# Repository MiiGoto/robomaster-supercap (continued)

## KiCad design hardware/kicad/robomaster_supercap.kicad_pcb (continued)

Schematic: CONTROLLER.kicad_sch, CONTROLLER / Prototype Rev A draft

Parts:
C40, C41, C42, C43, C46, C48: 100nF / 16V X7R; C_0805_2012Metric; MPN C0805C104K5RACTU
C44: 4.7uF /16V X7R; C_0805_2012Metric; MPN C0805C475K4RACTU
C45, C47: 1uF /16V; C_0805_2012Metric; MPN GRM21BR71H105KA12L
C49: 100nF; C_0805_2012Metric; MPN C0805C104K5RACTU
J6: SWD reference voltage ONLY / do not externally po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; PinHeader_1x06_P2.54mm_Vertical
J7: 3.3V UART / no power pin; PinHeader_1x03_P2.54mm_Vertical
R69: 10R; R_0805_2012Metric; MPN CRCW080510R0FKEA
R70: 0R; R_0805_2012Metric; MPN CRCW08050000Z0EA
R71, R72, R73, R74, R75, R76, R77, R78, R79, R80, R81: 10k; R_0805_2012Metric; MPN CRCW080510K0FKEA
U11: STM32G474RET6; LQFP-64_10x10mm_P0.5mm; MPN STM32G474RET6

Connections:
ARM_PULSE: R77.1 (A), U11.24 (PB0); also elsewhere on the board
BUS_ISO_FB: U11.57 (PB4); also elsewhere on the board
BUS_ISO_REQUEST: U11.38 (PC6); also elsewhere on the board
BUS_I_ADC: U11.18 (PA4); also elsewhere on the board
BUS_RAW_ADC: U11.11 (PC3); also elsewhere on the board
BUS_V_ADC: U11.12 (PA0); also elsewhere on the board
BYP_BUS_FB: U11.59 (PB6); also elsewhere on the board
BYP_BUS_REQUEST: U11.33 (PB11); also elsewhere on the board
BYP_CAP_FB: U11.60 (PB7); also elsewhere on the board
BYP_CAP_REQUEST: U11.41 (PC9); also elsewhere on the board
CAN_RX: R72.1 (A), U11.61 (PB8); also elsewhere on the board
CAN_STANDBY: U11.54 (PC12); also elsewhere on the board
CAN_TX: U11.62 (PB9); also elsewhere on the board
CAP_ISO_FB: U11.58 (PB5); also elsewhere on the board
CAP_ISO_REQUEST: U11.39 (PC7); also elsewhere on the board
CAP_I_ADC: U11.19 (PA5); also elsewhere on the board
CAP_RAW_ADC: U11.22 (PC4); also elsewhere on the board
CAP_V_ADC: U11.13 (PA1); also elsewhere on the board
DUMP_REQUEST: U11.52 (PC10); also elsewhere on the board
GND: C40.2 (B), C41.2 (B), C42.2 (B), C43.2 (B), C44.2 (B), C45.2 (B), C46.2 (B), C47.2 (B), C48.2 (B), C49.2 (B), J6.6, J7.3, R73.2 (B), R74.2 (B), R75.2 (B), R76.2 (B), R77.2 (B), R78.2 (B), R79.2 (B), R80.2 (B), U11.15 (VSS), U11.27 (VSSA), U11.31 (VSS), U11.47 (VSS), U11.63 (VSS); also elsewhere on the board
HW_FAULT_N: U11.46 (PA12); also elsewhere on the board
IL_I_ADC: U11.20 (PA6); also elsewhere on the board
MCU_GATE_REQUEST: R78.1 (A), U11.26 (PB2); also elsewhere on the board
MON_ALERT_HOST: U11.53 (PC11); also elsewhere on the board
MON_CONFIG_VALID: R80.1 (A), U11.55 (PD2); also elsewhere on the board
MON_CS_HOST: R81.1 (A), U11.34 (PB12); also elsewhere on the board
MON_MISO_HOST: U11.36 (PB14); also elsewhere on the board
MON_MOSI_HOST: U11.37 (PB15); also elsewhere on the board
MON_SCLK_HOST: U11.35 (PB13); also elsewhere on the board
NRST: C49.1 (A), J6.5, R71.1 (A), U11.7 (PG10); also elsewhere on the board
PRE_BUS_FB: U11.51 (PA15); also elsewhere on the board
PRE_BUS_REQUEST: U11.30 (PB10); also elsewhere on the board
PRE_CAP_FB: U11.2 (PC13); also elsewhere on the board
PRE_CAP_REQUEST: U11.40 (PC8); also elsewhere on the board
PWM_AH: R73.1 (A), U11.42 (PA8); also elsewhere on the board
PWM_AL: R74.1 (A), U11.43 (PA9); also elsewhere on the board
PWM_BH: R75.1 (A), U11.44 (PA10); also elsewhere on the board
PWM_BL: R76.1 (A), U11.45 (PA11); also elsewhere on the board
REFEREE_PERMIT: U11.23 (PC5); also elsewhere on the board
SWCLK: J6.3, U11.50 (PA14)
SWDIO: J6.2, U11.49 (PA13)
SWO: J6.4, U11.56 (PB3)
TEMP_BANK_ADC: U11.10 (PC2); also elsewhere on the board
TEMP_FET_ADC: U11.8 (PC0); also elsewhere on the board
TEMP_L_ADC: U11.9 (PC1); also elsewhere on the board
UART_RX: J7.2, U11.17 (PA3)
UART_TX: J7.1, U11.14 (PA2)
V3V3: C40.1 (A), C41.1 (A), C42.1 (A), C43.1 (A), C44.1 (A), J6.1, R69.1 (A), R71.2 (B), R72.2 (B), R81.2 (B), U11.1 (VBAT), U11.16 (VDD), U11.32 (VDD), U11.48 (VDD), U11.64 (VDD); also elsewhere on the board
VDDA: C45.1 (A), C46.1 (A), R69.2 (B), R70.1 (A), U11.29 (VDDA)
VREF_ADC: C47.1 (A), C48.1 (A), R70.2 (B), U11.28 (VREF+)
WD_HEARTBEAT: R79.1 (A), U11.25 (PB1); also elsewhere on the board

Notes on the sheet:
PG10 pin7 configured NRST; PB8 pin61 BOOT0 strap/options: boot configuration must be locked to flash before use.
HSI clock for draft, no external crystal. FDCAN bit timing/HSI accuracy must be checked before robot integration.
ADC HRTIM-synchronized sampling; internal comparators are secondary diagnostics, not primary OC shutdown.

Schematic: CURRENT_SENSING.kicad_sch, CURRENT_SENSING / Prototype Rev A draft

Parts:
C50, C52, C53, C54, C56, C57, C58, C60, C61: 100nF / 16V X7R; C_0805_2012Metric; MPN C0805C104K5RACTU
C51, C55, C59: 1nF C0G; C_0805_2012Metric; MPN C0805C102J1GACTU
J8: OC diagnostic outputs / do not load; PinHeader_1x05_P2.54mm_Vertical
R82, R83, R84: 100R; R_0805_2012Metric; MPN CRCW0805100RFKEA
U12: INA240A2D; SOIC-8_3.9x4.9mm_P1.27mm; MPN INA240A2D
U13, U14, U16, U17, U19, U20: INA293A1DBVR; SOT-23-5; MPN INA293A1DBVR
U15, U18: INA240A1D; SOIC-8_3.9x4.9mm_P1.27mm; MPN INA240A1D

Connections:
BUS_FAST_NEG: J8.2, U14.1 (OUT); also elsewhere on the board
BUS_FAST_POS: J8.1, U13.1 (OUT); also elsewhere on the board
BUS_I_FILTER: C51.1 (A), R82.2 (B); also elsewhere on the board
BUS_I_RAW: R82.1 (A), U12.5 (OUT)
BUS_KELVIN_M: U12.1 (INM), U13.4 (INM), U14.3 (INP); also elsewhere on the board
BUS_KELVIN_P: U12.8 (INP), U13.3 (INP), U14.4 (INM); also elsewhere on the board
CAP_FAST_NEG: J8.4, U17.1 (OUT); also elsewhere on the board
CAP_FAST_POS: J8.3, U16.1 (OUT); also elsewhere on the board
CAP_I_FILTER: C55.1 (A), R83.2 (B); also elsewhere on the board
CAP_I_RAW: R83.1 (A), U15.5 (OUT)
CAP_KELVIN_M: U15.1 (INM), U16.4 (INM), U17.3 (INP); also elsewhere on the board
CAP_KELVIN_P: U15.8 (INP), U16.3 (INP), U17.4 (INM); also elsewhere on the board
GND: C50.2 (B), C51.2 (B), C52.2 (B), C53.2 (B), C54.2 (B), C55.2 (B), C56.2 (B), C57.2 (B), C58.2 (B), C59.2 (B), C60.2 (B), C61.2 (B), J8.5, U12.2 (GND), U12.3 (REF2), U13.2 (GND), U14.2 (GND), U15.2 (GND), U15.3 (REF2), U16.2 (GND), U17.2 (GND), U18.2 (GND), U18.3 (REF2), U19.2 (GND), U20.2 (GND); also elsewhere on the board
IL_FAST_NEG: U20.1 (OUT); also elsewhere on the board
IL_FAST_POS: U19.1 (OUT); also elsewhere on the board
IL_I_FILTER: C59.1 (A), R84.2 (B); also elsewhere on the board
IL_I_RAW: R84.1 (A), U18.5 (OUT)
IL_KELVIN_M: U18.1 (INM), U19.4 (INM), U20.3 (INP); also elsewhere on the board
IL_KELVIN_P: U18.8 (INP), U19.3 (INP), U20.4 (INM); also elsewhere on the board
V3V3: C50.1 (A), C52.1 (A), C53.1 (A), C54.1 (A), C56.1 (A), C57.1 (A), C58.1 (A), C60.1 (A), C61.1 (A), U12.6 (VS), U12.7 (REF1), U13.5 (VS), U14.5 (VS), U15.6 (VS), U15.7 (REF1), U16.5 (VS), U17.5 (VS), U18.6 (VS), U18.7 (REF1), U19.5 (VS), U20.5 (VS); also elsewhere on the board

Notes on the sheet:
WSK Kelvin pads2/3 route separately to amplifiers; no power current in sense tracks.
INA240 refs REF1=VS, REF2=GND -> midscale1.65V. +-8A bus and +-20A cap/IL nominal ADC windows.
All fast front ends INA293 CM -4..110V; INA301 rejected because40V absmax is below SMBJ28A45.4V rated clamp.
IL dedicated INA293 opposite polarities, CM -4..110V; PWM edge recovery and latency must be measured.

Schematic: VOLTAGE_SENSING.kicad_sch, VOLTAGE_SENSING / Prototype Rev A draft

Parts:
C62, C63, C64, C65: 4.7nF C0G; C_0805_2012Metric; MPN C0805C472J5GACTU
C66, C67, C68: 100nF / 16V X7R; C_0805_2012Metric; MPN C0805C104K5RACTU
D13, D15, D17, D19: BAT54H signal clamp; D_SOD-123F; MPN BAT54H
D14, D16, D18, D20: BAT54H negative clamp; D_SOD-123F; MPN BAT54H
D21, D22: 1N4148W /100V; D_SOD-123; MPN 1N4148W
R85, R86, R88, R89, R91, R92, R94, R95: 33k /1%; R_0805_2012Metric; MPN CRCW080533K0FKEA
R87, R93: 5.1k /1%; R_0805_2012Metric; MPN CRCW08055K10FKEA
R90, R96: 6.8k /1%; R_0805_2012Metric; MPN CRCW08056K80FKEA
R97: 3.3k /1W; R_2512_6332Metric; MPN CRCW25123K30FKEG
R98: 11.8k /1%; R_0805_2012Metric; MPN CRCW080511K8FKEA
R99: 10k /1%; R_0805_2012Metric; MPN CRCW080510K0FKEA
R100, R101, R102, R103, R104, R105, R106, R107, R108, R109: 100k off leakage drain; R_0805_2012Metric; MPN CRCW0805100KFKEA
U21: TLV431AIDBZR; SOT-23; MPN TLV431AIDBZR
U22, U23, U24: TMUX1511PWR; TSSOP-14_4.4x5mm_P0.65mm; MPN TMUX1511PWR

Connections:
ADC_CLAMP_2V7: D13.1 (K), D15.1 (K), D17.1 (K), D19.1 (K), R97.2 (B), R98.1 (A), U21.2 (K)
BANK_P_RAW: D22.2 (A), R94.1 (A); also elsewhere on the board
BUS_DIV_TOP: R85.2 (B), R86.1 (A)
BUS_FUSED: D21.2 (A), R91.1 (A); also elsewhere on the board
BUS_I_ADC: R104.1 (A), U23.3 (D1); also elsewhere on the board
BUS_I_FILTER: U23.2 (S1); also elsewhere on the board
BUS_LINK: R85.1 (A); also elsewhere on the board
BUS_RAW_ADC: R102.1 (A), U22.8 (D3); also elsewhere on the board
BUS_RAW_DIV_TOP: R91.2 (B), R92.1 (A)
BUS_RAW_V_FILTER: C64.1 (A), D17.2 (A), D18.1 (K), R92.2 (B), R93.1 (A), U22.9 (S3)
BUS_V_ADC: R100.1 (A), U22.3 (D1); also elsewhere on the board
BUS_V_FILTER: C62.1 (A), D13.2 (A), D14.1 (K), R86.2 (B), R87.1 (A), U22.2 (S1)
CAP_DIV_TOP: R88.2 (B), R89.1 (A)
CAP_I_ADC: R105.1 (A), U23.6 (D2); also elsewhere on the board
CAP_I_FILTER: U23.5 (S2); also elsewhere on the board
CAP_LINK: R88.1 (A); also elsewhere on the board
CAP_RAW_ADC: R103.1 (A), U22.11 (D4); also elsewhere on the board
CAP_RAW_DIV_TOP: R94.2 (B), R95.1 (A)
CAP_RAW_V_FILTER: C65.1 (A), D19.2 (A), D20.1 (K), R95.2 (B), R96.1 (A), U22.12 (S4)
CAP_V_ADC: R101.1 (A), U22.6 (D2); also elsewhere on the board
CAP_V_FILTER: C63.1 (A), D15.2 (A), D16.1 (K), R89.2 (B), R90.1 (A), U22.5 (S2)
CLAMP_OR: D21.1 (K), D22.1 (K), R97.1 (A)
CLAMP_REF: R98.2 (B), R99.1 (A), U21.1 (REF)
GND: C62.2 (B), C63.2 (B), C64.2 (B), C65.2 (B), C66.2 (B), C67.2 (B), C68.2 (B), D14.2 (A), D16.2 (A), D18.2 (A), D20.2 (A), R87.2 (B), R90.2 (B), R93.2 (B), R96.2 (B), R99.2 (B), R100.2 (B), R101.2 (B), R102.2 (B), R103.2 (B), R104.2 (B), R105.2 (B), R106.2 (B), R107.2 (B), R108.2 (B), R109.2 (B), U21.3 (A), U22.7 (GND), U23.7 (GND), U24.7 (GND), U24.9 (S3), U24.12 (S4); also elsewhere on the board
IL_I_ADC: R106.1 (A), U23.8 (D3); also elsewhere on the board
IL_I_FILTER: U23.9 (S3); also elsewhere on the board
RAIL_OK: U22.1 (SEL1), U22.4 (SEL2), U22.10 (SEL3), U22.13 (SEL4), U23.1 (SEL1), U23.4 (SEL2), U23.10 (SEL3), U23.13 (SEL4), U24.1 (SEL1), U24.4 (SEL2), U24.10 (SEL3), U24.13 (SEL4); also elsewhere on the board
TEMP_BANK_ADC: R109.1 (A), U24.6 (D2); also elsewhere on the board
TEMP_BANK_FILTER: U24.5 (S2); also elsewhere on the board
TEMP_FET_ADC: R107.1 (A), U23.11 (D4); also elsewhere on the board
TEMP_FET_FILTER: U23.12 (S4); also elsewhere on the board
TEMP_L_ADC: R108.1 (A), U24.3 (D1); also elsewhere on the board
TEMP_L_FILTER: U24.2 (S1); also elsewhere on the board
V3V3: C66.1 (A), C67.1 (A), C68.1 (A), U22.14 (VDD), U23.14 (VDD), U24.14 (VDD); also elsewhere on the board

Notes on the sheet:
TMUX1511 powered-off isolation <=3.6V; independent 2.7V clamp proposal avoids dumping into dead MCU rail.
Divider bus36V ->2.582V; cap24.3V ->2.270V nominal. Clamp forward-V and all partial-power cases MUST VERIFY.
100k ADC-side drain:2uA max powered-off leakage gives0.2V estimate. Include loaded divider/NTC calibration.
Current/NTC outputs are bus-fed; partial-power/backfeed and probe effects remain test gates.

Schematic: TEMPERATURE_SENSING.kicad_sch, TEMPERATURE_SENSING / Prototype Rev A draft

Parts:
C69, C70, C71: 10nF; C_0805_2012Metric; MPN C0805C103J5GACTU
J9: FET NTC probe option; PinHeader_1x02_P2.54mm_Vertical; not fitted
J10: L NTC probe option; PinHeader_1x02_P2.54mm_Vertical; not fitted
J11: BANK NTC probe option; PinHeader_1x02_P2.54mm_Vertical; not fitted
R110, R112, R114: 10k /1%; R_0805_2012Metric; MPN CRCW080510K0FKEA
R111, R113, R115: NTCLE100E3103JB0 /10k NTC B3977; PinHeader_1x02_P2.54mm_Vertical; MPN NTCLE100E3103JB0

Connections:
GND: C69.2 (B), C70.2 (B), C71.2 (B), J9.2, J10.2, J11.2, R111.2 (B), R113.2 (B), R115.2 (B); also elsewhere on the board
TEMP_BANK_FILTER: C71.1 (A), J11.1, R114.2 (B), R115.1 (A); also elsewhere on the board
TEMP_FET_FILTER: C69.1 (A), J9.1, R110.2 (B), R111.1 (A); also elsewhere on the board
TEMP_L_FILTER: C70.1 (A), J10.1, R112.2 (B), R113.1 (A); also elsewhere on the board
V3V3: R110.1 (A), R112.1 (A), R114.1 (A); also elsewhere on the board

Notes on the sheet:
3 representative hotspots; optional connector replaces fitted NTC, not parallel second thermistor.
Open NTC reads high, short reads zero. Firmware faults both extremes; hardware thermal window also in SAFETY.
Trip reference options: bank ~55C, FET/L ~70C investigation only; hotspot-to-junction lag unresolved.

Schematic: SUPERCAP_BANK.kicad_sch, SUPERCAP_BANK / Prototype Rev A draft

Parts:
C72, C73, C74, C75, C76, C77, C78, C79, C80: 50F /2.7V SCCV40B506SRB / external cell; MPN SCCV40B506SRB
C81, C82, C83, C84, C85, C86, C87, C88, C89: 100nF /50V X7R; C_0805_2012Metric; MPN C0805C104K5RACTU
C90, C91, C92, C93, C94: 100nF / 16V X7R; C_0805_2012Metric; MPN C0805C104K5RACTU
C95: 1uF /50V X7R; C_0805_2012Metric; MPN GRM21BR71H105KA12L
C96, C97, C98: 1uF /16V; C_0805_2012Metric; MPN GRM21BR71H105KA12L
D23: SMBJ18CA bidirectional coil suppression / release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; D_SMB; MPN SMBJ18CA
F3: 0997015.WXN / MINI997 58V15A / external 0FHM0002Z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; MPN 0997015.WXN
J12: 9S bank power -> official module external boundary
J13: CAP_ISO actuator+reserved diagnostic / no intrins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
J14: Protected 9S taps / source resistors at electrode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
K4: CAP_ISO external NO contact / AEV14012 bench sele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; MPN AEV14012
Q16: CSD18540Q5B; VSONP-8-1EP_5x6_P1.27mm; MPN CSD18540Q5B
Q17: BC857B; SOT-23; MPN BC857B,215
Q18: BC847B; SOT-23; MPN BC847B,215
Q19: BC847B preregulator / voltage thermal MUST VERIFY; SOT-23; MPN BC847B,215
R116, R117, R118, R122, R143, R144, R145, R146, R147, R150, R151, R155, R156: 10k; R_0805_2012Metric; MPN CRCW080510K0FKEA
R119: 4.7k; R_0805_2012Metric; MPN CRCW08054K70FKEA
R120: 100k; R_0805_2012Metric; MPN CRCW0805100KFKEA
R121: 47R; R_0805_2012Metric; MPN CRCW080547R0FKEA
R123, R124, R125, R126, R127, R128, R129, R130, R131, R132: 1k /1W EXTERNAL cell-terminal tap resistor; MPN CRCW25121K00FKEG
R133, R134, R135, R136, R137, R138, R139, R140, R141, R142: 1k /1W tap protection / no bypass; R_2512_6332Metric; MPN CRCW25121K00FKEG
R148: 100R; R_0805_2012Metric; MPN CRCW0805100RFKEA
R149: 0R; R_0805_2012Metric; MPN CRCW08050000Z0EA
R152, R153, R154: 10k TS commissioning option; R_0805_2012Metric; MPN CRCW080510K0FKEA
U25: Blue Sea6006 / external manual bank disconnect;no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; MPN 6006
U26: BQ7694204PFBR; TQFP-48_7x7mm_P0.5mm; MPN BQ7694204PFBR
U27: SN74LV1T34DBVR; SOT-23-5; MPN SN74LV1T34DBVR
U28: TPS3839K33DBZR; SOT-23; MPN TPS3839K33DBZR
U29: SN74LVC2G08DCUR; VSSOP-8_2.3x2mm_P0.5mm; MPN SN74LVC2G08DCUR
U30, U31: TMUX1511PWR; TSSOP-14_4.4x5mm_P0.65mm; MPN TMUX1511PWR

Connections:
ACTUATOR_12V: D23.1 (K), J13.1, K4.3 (COIL_P), Q17.2 (E), R117.2 (B); also elsewhere on the board
BANK_P_RAW: C80.1 (A), J12.1, R132.1 (A), R148.1 (A), R150.1 (A), R151.1 (A), U25.1 (COM); also elsewhere on the board
CAP_ISO_COIL_GATE: Q16.2 (G_DS4), R116.1 (A), R121.2 (B)
CAP_ISO_COIL_M: D23.2 (A), J13.2, K4.4 (COIL_M), Q16.3 (D_DS5_6_7_8); also elsewhere on the board
CAP_ISO_DRIVE: R119.1 (A); also elsewhere on the board
CAP_ISO_FB: J13.3, R122.1 (A); also elsewhere on the board
CAP_ISO_NPN_C: Q18.3 (C), R118.2 (B)
CAP_ISO_NPN_C_BASE: Q18.1 (B), R119.2 (B), R120.1 (A)
CAP_ISO_PNP_B: Q17.1 (B), R117.1 (A), R118.1 (A)
CAP_ISO_PNP_C: Q17.3 (C), R121.1 (A)
CELL0_FILTER: C81.2 (B), R133.2 (B), U26.16 (VC0)
CELL1_FILTER: C81.1 (A), C82.2 (B), R134.2 (B), U26.15 (VC1)
CELL2_FILTER: C82.1 (A), C83.2 (B), R135.2 (B), U26.14 (VC2)
CELL3_FILTER: C83.1 (A), C84.2 (B), R136.2 (B), U26.13 (VC3)
CELL4_FILTER: C84.1 (A), C85.2 (B), R137.2 (B), U26.12 (VC4)
CELL5_FILTER: C85.1 (A), C86.2 (B), R138.2 (B), U26.10 (VC5)
CELL6_FILTER: C86.1 (A), C87.2 (B), R139.2 (B), U26.8 (VC6)
CELL7_FILTER: C87.1 (A), C88.2 (B), R140.2 (B), U26.6 (VC7)
CELL8_FILTER: C88.1 (A), C89.2 (B), R141.2 (B), U26.2 (VC9), U26.4 (VC8)
CELL9_FILTER: C89.1 (A), R142.2 (B), U26.48 (VC10)
GND: C72.2 (B), C90.2 (B), C91.2 (B), C92.2 (B), C93.2 (B), C94.2 (B), C95.2 (B), C96.2 (B), C97.2 (B), C98.2 (B), J12.2, J13.4, Q16.1 (S_DS1_2_3), Q18.2 (E), R116.2 (B), R120.2 (B), R122.2 (B), R123.1 (A), R143.2 (B), R146.2 (B), R147.2 (B), R152.2 (B), R153.2 (B), R154.2 (B), R155.2 (B), R156.2 (B), U26.17 (VSS), U26.18 (SRP), U26.20 (SRN), U26.30 (DFETOFF), U26.33 (RST_SHUT), U27.3 (GND), U28.1 (GND), U29.4 (GND), U29.5 (A2), U29.6 (B2), U30.7 (GND), U31.5 (S2), U31.7 (GND), U31.9 (S3), U31.12 (S4); also elsewhere on the board
MON_ALERT: R144.1 (A), U26.25 (ALERT), U31.2 (S1)
MON_ALERT_HOST: U31.3 (D1); also elsewhere on the board
MON_BAT: C95.1 (A), Q19.3 (C), R148.2 (B), R149.2 (B), U26.47 (BAT)
MON_BREG: Q19.1 (B), U26.37 (BREG)
MON_COMM_PERMIT: U29.7 (Y1), U30.1 (SEL1), U30.4 (SEL2), U30.10 (SEL3), U30.13 (SEL4), U31.1 (SEL1), U31.4 (SEL2), U31.10 (SEL3), U31.13 (SEL4)
MON_CP: R149.1 (A), U26.46 (CP1)
MON_CS: R145.1 (A), U26.29 (CS_N), U30.8 (D3)
MON_CS_HOST: U30.9 (S3); also elsewhere on the board
MON_DCHG: R155.1 (A), U26.31 (DCHG); also elsewhere on the board
MON_DDSG: R156.1 (A), U26.32 (DDSG); also elsewhere on the board
MON_LD: R151.2 (B), U26.41 (LD)
MON_MISO: R143.1 (A), U26.27 (MISO), U27.2 (A)
MON_MISO_HOST: U30.11 (D4); also elsewhere on the board
MON_MISO_SHIFTED: U27.4 (Y), U30.12 (S4)
MON_MOSI: R147.1 (A), U26.28 (MOSI), U30.6 (D2)
MON_MOSI_HOST: U30.5 (S2); also elsewhere on the board
MON_PACK: R150.2 (B), U26.42 (PACK)
MON_POWER_OK: U28.2 (RESET_N), U29.2 (B1)
MON_REG1: C90.1 (A), C91.1 (A), C97.1 (A), R144.2 (B), R145.2 (B), U26.35 (REG1), U27.5 (VCC), U28.3 (VDD)
MON_REG18: C98.1 (A), U26.24 (REG18)
MON_REGIN: C96.1 (A), Q19.2 (E), U26.36 (REGIN)
MON_SCLK: R146.1 (A), U26.26 (SCLK), U30.3 (D1)
MON_SCLK_HOST: U30.2 (S1); also elsewhere on the board
MON_TS1: R152.1 (A), U26.21 (TS1)
MON_TS2: R153.1 (A), U26.22 (TS2)
MON_TS3: R154.1 (A), U26.23 (TS3)
unnamed: C72.1 (A), C73.2 (B), R124.1 (A)
unnamed: C73.1 (A), C74.2 (B), R125.1 (A)
unnamed: C74.1 (A), C75.2 (B), R126.1 (A)
unnamed: C75.1 (A), C76.2 (B), R127.1 (A)
unnamed: C76.1 (A), C77.2 (B), R128.1 (A)
unnamed: C77.1 (A), C78.2 (B), R129.1 (A)
unnamed: C78.1 (A), C79.2 (B), R130.1 (A)
unnamed: C79.1 (A), C80.2 (B), R131.1 (A)
unnamed: F3.1 (A), U25.2 (SWITCHED)
unnamed: F3.2 (B), K4.1 (COM)
RAIL_OK: U29.1 (A1); also elsewhere on the board
TAP0_SOURCE_PROTECTED: J14.1, R123.2 (B), R133.1 (A); also elsewhere on the board
TAP1_SOURCE_PROTECTED: J14.2, R124.2 (B), R134.1 (A); also elsewhere on the board
TAP2_SOURCE_PROTECTED: J14.3, R125.2 (B), R135.1 (A); also elsewhere on the board
TAP3_SOURCE_PROTECTED: J14.4, R126.2 (B), R136.1 (A); also elsewhere on the board
TAP4_SOURCE_PROTECTED: J14.5, R127.2 (B), R137.1 (A); also elsewhere on the board
TAP5_SOURCE_PROTECTED: J14.6, R128.2 (B), R138.1 (A); also elsewhere on the board
TAP6_SOURCE_PROTECTED: J14.7, R129.2 (B), R139.1 (A); also elsewhere on the board
TAP7_SOURCE_PROTECTED: J14.8, R130.2 (B), R140.1 (A); also elsewhere on the board
TAP8_SOURCE_PROTECTED: J14.9, R131.2 (B), R141.1 (A); also elsewhere on the board
TAP9_SOURCE_PROTECTED: J14.10, R132.2 (B), R142.1 (A); also elsewhere on the board
V3V3: C92.1 (A), C93.1 (A), C94.1 (A), U29.8 (VCC), U30.14 (VDD), U31.14 (VDD); also elsewhere on the board

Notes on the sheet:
BQ7694204 SPI/CRC +3.3V REG1 variant. 9S mask: cells1..8 +cell10, VC9 tied to VC8, unused cell9 disabled.
RAM profile firmware/config/bq76942_rev_a.json: COV2.530V, CUV1.2144V, delay~10ms; readback mandatory.
DCHG/DDSG active-LOW fault / healthy-HIGH REG1 permission,0xA6,pull-down. Never use Li-ion defaults.
Host-only balance,2k total input resistance/tap including external1k; slow trim,not full-current balancing.
Open-wire current/settling plus input R must be validated; harness source protection before connector is mandatory.
TMUX SPI/ALERT disconnect if either MCU or REG1 power missing; LV1T34 handles initial1.8V MISO level.
BQ battery-ground SPI is not galvanically isolated; partial-power/backfeed review still mandatory.

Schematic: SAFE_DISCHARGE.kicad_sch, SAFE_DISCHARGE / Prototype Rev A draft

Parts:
D24: BZT52H-C15; D_SOD-123F; MPN BZT52H-C15
D25: red residual-energy indicator / bank-powered; LED_0805_2012Metric; MPN LTST-C170KRKT
J15: KEYED service meter / rated discharge tool connec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
Q20: CSD18540Q5B; VSONP-8-1EP_5x6_P1.27mm; MPN CSD18540Q5B
Q21: BC857B; SOT-23; MPN BC857B,215
Q22: BC847B; SOT-23; MPN BC847B,215
R157: 10k /1W permanent bleed; R_2512_6332Metric; MPN CRCW251210K0FKEG
R158: 100R /HS25 100R F / external chassis mount; MPN HS25 100R F
R159, R161, R162: 10k; R_0805_2012Metric; MPN CRCW080510K0FKEA
R160: 47R; R_0805_2012Metric; MPN CRCW080547R0FKEA
R163: 4.7k; R_0805_2012Metric; MPN CRCW08054K70FKEA
R164: 100k; R_0805_2012Metric; MPN CRCW0805100KFKEA
R165: 22k /0.25W; R_0805_2012Metric; MPN CRCW080522K0FKEA
R166: 100R / HS25 100R F / external service tool; MPN HS25 100R F
U32: Blue Sea6006 / external independent service tool;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; MPN 6006

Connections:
BANK_P_RAW: J15.1, R157.1 (A), R158.1 (A), R165.1 (A), U32.1 (COM); also elsewhere on the board
DUMP_DRAIN: Q20.3 (D_DS5_6_7_8), R158.2 (B); also elsewhere on the board
DUMP_DRIVE: R163.1 (A); also elsewhere on the board
DUMP_GATE: D24.1 (K), Q20.2 (G_DS4), R159.1 (A), R160.2 (B)
DUMP_NPN_C: Q22.3 (C), R162.2 (B)
DUMP_NPN_C_BASE: Q22.1 (B), R163.2 (B), R164.1 (A)
DUMP_PNP_B: Q21.1 (B), R161.1 (A), R162.1 (A)
DUMP_PNP_C: Q21.3 (C), R160.1 (A)
GND: D24.2 (A), D25.1 (K), J15.2, Q20.1 (S_DS1_2_3), Q22.2 (E), R157.2 (B), R159.2 (B), R164.2 (B), R166.2 (B); also elsewhere on the board
unnamed: R166.1 (A), U32.2 (SWITCHED)
RESIDUAL_LED_A: D25.2 (A), R165.2 (B)
V12_DRIVER: Q21.2 (E), R161.2 (B); also elsewhere on the board

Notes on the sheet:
OFF is not safe. LED dark is not safe. Independent meter + all cells + local links + rebound required.
Switched100R initial4.862W, energy up to1752J(+30%); 10k bleed alone ~62h to1V. No guaranteed service time.
Dump unavailable after bus aux loss: permanent bleed + independent service tool remain; do not add unauthorized bank-to-bus supply.
DUMP_DRIVE requires temperature permission; MOSFET-short leaves100R permanently on, resistor thermal review mandatory.

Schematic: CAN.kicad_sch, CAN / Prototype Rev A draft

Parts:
C99: 100nF / 16V X7R; C_0805_2012Metric; MPN C0805C104K5RACTU
J16: robot telemetry CAN / official module CAN separate
J17: selectable termination shunt, fit only at bus end; PinHeader_1x02_P2.54mm_Vertical
R167, R168: 10k; R_0805_2012Metric; MPN CRCW080510K0FKEA
R169: 120R /1%; R_0805_2012Metric; MPN CRCW0805120RFKEA
U33: SN65HVD230DR; SOIC-8_3.9x4.9mm_P1.27mm; MPN SN65HVD230DR

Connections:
CAN_H: J16.1, R169.1 (A), U33.7 (CANH); also elsewhere on the board
CAN_L: J16.2, J17.2, U33.6 (CANL); also elsewhere on the board
CAN_RX: U33.4 (R); also elsewhere on the board
CAN_STANDBY: R168.1 (A), U33.8 (RS); also elsewhere on the board
CAN_TERM: J17.1, R169.2 (B)
CAN_TX: R167.1 (A), U33.1 (D); also elsewhere on the board
GND: C99.2 (B), J16.3, U33.2 (GND); also elsewhere on the board
V3V3: C99.1 (A), R167.2 (B), R168.2 (B), U33.3 (VCC); also elsewhere on the board

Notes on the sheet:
Classic CAN initial protocol, bitrate/ID/timeouts TBD. CAN comm must not bypass official cutoff.
CAN powered-off impedance/common-mode protection and external power through UART/SWD/taps require validation.

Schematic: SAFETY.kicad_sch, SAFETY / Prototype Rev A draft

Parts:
C100, C101, C102, C103, C104, C105, C106, C107, C108, C109, C110, C111, C112, C113, C114, C115, C116, C117, C118, C119, C120, C121, C122, C123, C124, C125, C126, C127, C128, C129, C133, C134, C135, C136, C137, C138, C139, C140: 100nF / 16V X7R; C_0805_2012Metric; MPN C0805C104K5RACTU
C130, C131, C132: 1nF /50V; C_0805_2012Metric; MPN C0805C102J1GACTU
J18: latched fault diagnostic output; PinHeader_1x02_P2.54mm_Vertical
R170: 58.7k /1%; R_0805_2012Metric; MPN CRCW080558K7FKEA
R171, R173: 10k /PROVISIONAL; R_0805_2012Metric; MPN CRCW080510K0FKEA
R172: 35.7k /1%; R_0805_2012Metric; MPN CRCW080535K7FKEA
R174: 35.7k; R_0805_2012Metric; MPN CRCW080535K7FKEA
R175: 10k / IL12.035A PROVISIONAL; R_0805_2012Metric; MPN CRCW080510K0FKEA
R176, R178, R179, R180, R181, R182, R183, R184, R185, R186, R188, R190, R193, R202, R204, R206, R208: 10k; R_0805_2012Metric; MPN CRCW080510K0FKEA
R177: 10k / preset timeout; verify SET1 table; R_0805_2012Metric; MPN CRCW080510K0FKEA
R187, R189: 1.74k /PROVISIONAL; R_0805_2012Metric; MPN CRCW08051K74FKEA
R191: 3.01k /PROVISIONAL; R_0805_2012Metric; MPN CRCW08053K01FKEA
R192: 1k; R_0805_2012Metric; MPN CRCW08051K00FKEA
R194: 2.2k; R_0805_2012Metric; MPN CRCW08052K20FKEA
R195: 221k /1%; R_0805_2012Metric; MPN CRCW0805221KFKEA
R196, R198, R200: 10k /1%; R_0805_2012Metric; MPN CRCW080510K0FKEA
R197: 154k /1%; R_0805_2012Metric; MPN CRCW0805154KFKEA
R199: 172k /1%; R_0805_2012Metric; MPN CRCW0805172KFKEA
R201: 80.6k; R_0805_2012Metric; MPN CRCW080580K6FKEA
R203, R207: 100k; R_0805_2012Metric; MPN CRCW0805100KFKEA
R205: 78.7k; R_0805_2012Metric; MPN CRCW080578K7FKEA
U34, U35, U38, U56, U58, U60, U65, U66, U69, U71: TLV3202DGKR; VSSOP-8_3x3mm_P0.65mm; MPN TLV3202DGKR
U36, U37, U39, U40, U43, U44, U45, U46, U48, U49, U50, U51, U52, U53, U54, U55, U57, U59, U61, U62, U63, U67, U68, U70, U72: SN74LVC2G08DCUR; VSSOP-8_2.3x2mm_P0.5mm; MPN SN74LVC2G08DCUR
U41: TPS3839K33DBZR; SOT-23; MPN TPS3839K33DBZR
U42: TPS3431SDRBR; VSON-8-1EP_3x3mm_P0.65mm_EP1.65x2.4mm; MPN TPS3431SDRBR
U47: SN74LVC1G74DCUR; VSSOP-8_2.3x2mm_P0.5mm; MPN SN74LVC1G74DCUR
U64: TLV431AIDBZR; SOT-23; MPN TLV431AIDBZR

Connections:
ACTUATOR_12V: R205.1 (A), R207.1 (A); also elsewhere on the board
ACTUATOR_OV_DIV: R207.2 (B), R208.1 (A), U71.6 (INM2)
ACTUATOR_OV_OK: U71.7 (OUT2), U72.2 (B1)
ACTUATOR_UV_DIV: R205.2 (B), R206.1 (A), U71.3 (INP1)
ACTUATOR_UV_OK: U71.1 (OUT1), U72.1 (A1)
ACTUATOR_WINDOW_OK: U72.6 (B2), U72.7 (Y1)
ALL_PROTECT_OK: U68.7 (Y1), U70.5 (A2)
ARM_PULSE: U47.1 (CLK); also elsewhere on the board
ASSEMBLY_PROTECT_OK: U45.5 (A2), U72.3 (Y2)
AUX_OK: U39.3 (Y2), U40.5 (A2)
BANK_OV_DIV: C132.1 (A), R199.2 (B), R200.1 (A), U66.2 (INM1)
BANK_OV_OK: U66.1 (OUT1), U67.6 (B2)
BANK_P_RAW: R199.1 (A); also elsewhere on the board
BANK_TEMP_HI_OK: U60.7 (OUT2), U61.2 (B1)
BANK_TEMP_LO_OK: U60.1 (OUT1), U61.1 (A1)
BANK_THERM_OK: U61.7 (Y1), U62.6 (B2)
BASE_OK: U44.3 (Y2), U45.1 (A1)
BUS_FAST_NEG: U34.6 (INM2); also elsewhere on the board
BUS_FAST_POS: U34.2 (INM1); also elsewhere on the board
BUS_FUSED: R195.1 (A), R197.1 (A); also elsewhere on the board
BUS_ISO_DRIVE: U50.7 (Y1); also elsewhere on the board
BUS_ISO_REQUEST: R180.1 (A), U50.1 (A1); also elsewhere on the board
BUS_LIMIT: R170.2 (B), R171.1 (A), U34.3 (INP1), U34.5 (INP2)
BUS_NEG_OK: U34.7 (OUT2), U36.2 (B1)
BUS_OC_OK: U36.7 (Y1), U37.1 (A1)
BUS_OV_DIV: C130.1 (A), R195.2 (B), R196.1 (A), U65.2 (INM1)
BUS_OV_OK: U65.1 (OUT1), U67.1 (A1)
BUS_POS_OK: U34.1 (OUT1), U36.1 (A1)
BUS_UV_DIV: C131.1 (A), R197.2 (B), R198.1 (A), U65.5 (INP2)
BUS_UV_OK: U65.7 (OUT2), U67.2 (B1)
BUS_WINDOW_OK: U67.5 (A2), U67.7 (Y1)
BYP_BUS_DRIVE: U53.7 (Y1); also elsewhere on the board
BYP_BUS_REQUEST: R183.1 (A), U53.1 (A1); also elsewhere on the board
BYP_CAP_DRIVE: U55.7 (Y1); also elsewhere on the board
BYP_CAP_REQUEST: R185.1 (A), U55.1 (A1); also elsewhere on the board
CAP_FAST_NEG: U35.6 (INM2); also elsewhere on the board
CAP_FAST_POS: U35.2 (INM1); also elsewhere on the board
CAP_ISO_DRIVE: U51.7 (Y1); also elsewhere on the board
CAP_ISO_REQUEST: R181.1 (A), U51.1 (A1); also elsewhere on the board
CAP_LIMIT: R172.2 (B), R173.1 (A), U35.3 (INP1), U35.5 (INP2)
CAP_NEG_OK: U35.7 (OUT2), U36.6 (B2)
CAP_OC_OK: U36.3 (Y2), U37.2 (B1)
CAP_POS_OK: U35.1 (OUT1), U36.5 (A2)
CELLS_HW_OK: U43.7 (Y1), U44.1 (A1)
CELLS_OK: U44.7 (Y1), U45.2 (B1)
CONTACT_PERMIT: U49.7 (Y1), U50.2 (B1), U51.2 (B1), U52.2 (B1), U53.2 (B1), U54.2 (B1), U55.2 (B1)
DRIVER_OV_DIV: R203.2 (B), R204.1 (A), U69.6 (INM2)
DRIVER_OV_OK: U69.7 (OUT2), U70.2 (B1)
DRIVER_PROTECT_OK: U70.3 (Y2), U72.5 (A2)
DRIVER_UV_DIV: R201.2 (B), R202.1 (A), U69.3 (INP1)
DRIVER_UV_OK: U69.1 (OUT1), U70.1 (A1)
DRIVER_WINDOW_OK: U70.6 (B2), U70.7 (Y1)
DUMP_DRIVE: U63.3 (Y2); also elsewhere on the board
DUMP_REQUEST: U63.5 (A2); also elsewhere on the board
FAST_OK: U43.3 (Y2), U44.5 (A2)
FAULT_CLEAR_N: U45.3 (Y2), U46.1 (A1), U48.2 (B1), U48.5 (A2), U49.2 (B1)
FAULT_LATCH_Q: R178.1 (A), U46.6 (B2), U47.5 (Q), U49.1 (A1)
FAULT_LATCH_QN: J18.1, U47.3 (QN)
FET_TEMP_HI_OK: U56.7 (OUT2), U57.2 (B1)
FET_TEMP_LO_OK: U56.1 (OUT1), U57.1 (A1)
FET_THERM_OK: U57.7 (Y1), U62.1 (A1)
GATE_PERMIT: R179.1 (A), U48.7 (Y1); also elsewhere on the board
GND: C100.2 (B), C101.2 (B), C102.2 (B), C103.2 (B), C104.2 (B), C105.2 (B), C106.2 (B), C107.2 (B), C108.2 (B), C109.2 (B), C110.2 (B), C111.2 (B), C112.2 (B), C113.2 (B), C114.2 (B), C115.2 (B), C116.2 (B), C117.2 (B), C118.2 (B), C119.2 (B), C120.2 (B), C121.2 (B), C122.2 (B), C123.2 (B), C124.2 (B), C125.2 (B), C126.2 (B), C127.2 (B), C128.2 (B), C129.2 (B), C130.2 (B), C131.2 (B), C132.2 (B), C133.2 (B), C134.2 (B), C135.2 (B), C136.2 (B), C137.2 (B), C138.2 (B), C139.2 (B), C140.2 (B), J18.2, R171.2 (B), R173.2 (B), R175.2 (B), R178.2 (B), R179.2 (B), R180.2 (B), R181.2 (B), R182.2 (B), R183.2 (B), R184.2 (B), R185.2 (B), R187.2 (B), R189.2 (B), R191.2 (B), R193.2 (B), R196.2 (B), R198.2 (B), R200.2 (B), R202.2 (B), R204.2 (B), R206.2 (B), R208.2 (B), U34.4 (GND), U35.4 (GND), U36.4 (GND), U37.4 (GND), U37.5 (A2), U37.6 (B2), U38.4 (GND), U39.4 (GND), U40.4 (GND), U41.1 (GND), U42.4 (GND), U42.9 (EP), U43.4 (GND), U44.4 (GND), U45.4 (GND), U46.4 (GND), U47.4 (GND), U48.4 (GND), U49.4 (GND), U49.5 (A2), U49.6 (B2), U50.4 (GND), U50.5 (A2), U50.6 (B2), U51.4 (GND), U51.5 (A2), U51.6 (B2), U52.4 (GND), U52.5 (A2), U52.6 (B2), U53.4 (GND), U53.5 (A2), U53.6 (B2), U54.4 (GND), U54.5 (A2), U54.6 (B2), U55.4 (GND), U55.5 (A2), U55.6 (B2), U56.4 (GND), U57.4 (GND), U57.5 (A2), U57.6 (B2), U58.4 (GND), U59.4 (GND), U59.5 (A2), U59.6 (B2), U60.4 (GND), U61.4 (GND), U61.5 (A2), U61.6 (B2), U62.4 (GND), U63.4 (GND), U64.3 (A), U65.4 (GND), U66.4 (GND), U66.5 (INP2), U67.4 (GND), U68.4 (GND), U68.5 (A2), U68.6 (B2), U69.4 (GND), U70.4 (GND), U71.4 (GND), U72.4 (GND); also elsewhere on the board
HW_FAULT_N: U48.3 (Y2); also elsewhere on the board
HW_REF_1V24: R194.2 (B), U64.1 (REF), U64.2 (K), U65.3 (INP1), U65.6 (INM2), U66.3 (INP1), U69.2 (INM1), U69.5 (INP2), U71.2 (INM1), U71.5 (INP2)
IL_FAST_NEG: U38.6 (INM2); also elsewhere on the board
IL_FAST_POS: U38.2 (INM1); also elsewhere on the board
IL_LIMIT: R174.2 (B), R175.1 (A), U38.3 (INP1), U38.5 (INP2)
IL_NEG_OK: U38.7 (OUT2), U39.2 (B1)
IL_OK: U39.7 (Y1), U40.1 (A1)
IL_POS_OK: U38.1 (OUT1), U39.1 (A1)
LATCH_CLEAR_N: U46.7 (Y1), U47.6 (CLR_N)
L_TEMP_HI_OK: U58.7 (OUT2), U59.2 (B1)
L_TEMP_LO_OK: U58.1 (OUT1), U59.1 (A1)
L_THERM_OK: U59.7 (Y1), U62.2 (B1)
MCU_GATE_REQUEST: U46.5 (A2); also elsewhere on the board
MON_CONFIG_VALID: U44.2 (B1); also elsewhere on the board
MON_DCHG: U43.1 (A1); also elsewhere on the board
MON_DDSG: U43.2 (B1); also elsewhere on the board
NRST: U46.2 (B1); also elsewhere on the board
OC_OK: U40.7 (Y1), U43.5 (A2)
PG_DRV: U39.5 (A2); also elsewhere on the board
PG_MCU: U39.6 (B2); also elsewhere on the board
PORT_OC_N: U37.7 (Y1), U40.2 (B1)
POWER_OK: U40.3 (Y2), U43.6 (B2)
POWER_THERM_OK: U62.5 (A2), U62.7 (Y1)
PRE_BUS_DRIVE: U52.7 (Y1); also elsewhere on the board
PRE_BUS_REQUEST: R182.1 (A), U52.1 (A1); also elsewhere on the board
PRE_CAP_DRIVE: U54.7 (Y1); also elsewhere on the board
PRE_CAP_REQUEST: R184.1 (A), U54.1 (A1); also elsewhere on the board
PROTECT_OK: U45.7 (Y1), U63.1 (A1)
RAILS_WINDOW_OK: U67.3 (Y2), U68.2 (B1)
RAIL_OK: U40.6 (B2), U41.2 (RESET_N); also elsewhere on the board
REFEREE_PERMIT: U45.6 (B2); also elsewhere on the board
REQUEST_PERMIT: U46.3 (Y2), U48.1 (A1)
TEMP_BANK_FILTER: U60.3 (INP1), U60.6 (INM2); also elsewhere on the board
TEMP_BANK_LIMIT: R190.2 (B), R191.1 (A), U60.2 (INM1)
TEMP_FET_FILTER: U56.3 (INP1), U56.6 (INM2); also elsewhere on the board
TEMP_FET_LIMIT: R186.2 (B), R187.1 (A), U56.2 (INM1)
TEMP_L_FILTER: U58.3 (INP1), U58.6 (INM2); also elsewhere on the board
TEMP_L_LIMIT: R188.2 (B), R189.1 (A), U58.2 (INM1)
TEMP_OPEN_LIMIT: R192.2 (B), R193.1 (A), U56.5 (INP2), U58.5 (INP2), U60.5 (INP2)
THERM_OK: U62.3 (Y2), U63.2 (B1), U63.6 (B2)
THERM_PROTECT_OK: U63.7 (Y1), U68.1 (A1)
V3V3: C100.1 (A), C101.1 (A), C102.1 (A), C103.1 (A), C104.1 (A), C105.1 (A), C106.1 (A), C107.1 (A), C108.1 (A), C109.1 (A), C110.1 (A), C111.1 (A), C112.1 (A), C113.1 (A), C114.1 (A), C115.1 (A), C116.1 (A), C117.1 (A), C118.1 (A), C119.1 (A), C120.1 (A), C121.1 (A), C122.1 (A), C123.1 (A), C124.1 (A), C125.1 (A), C126.1 (A), C127.1 (A), C128.1 (A), C129.1 (A), C133.1 (A), C134.1 (A), C135.1 (A), C136.1 (A), C137.1 (A), C138.1 (A), C139.1 (A), C140.1 (A), R170.1 (A), R172.1 (A), R174.1 (A), R176.2 (B), R177.2 (B), R186.1 (A), R188.1 (A), R190.1 (A), R192.1 (A), R194.1 (A), U34.8 (VCC), U35.8 (VCC), U36.8 (VCC), U37.8 (VCC), U38.8 (VCC), U39.8 (VCC), U40.8 (VCC), U41.3 (VDD), U42.1 (VDD), U42.3 (EN), U42.5 (SET1), U43.8 (VCC), U44.8 (VCC), U45.8 (VCC), U46.8 (VCC), U47.2 (D), U47.7 (PRE_N), U47.8 (VCC), U48.6 (B2), U48.8 (VCC), U49.8 (VCC), U50.8 (VCC), U51.8 (VCC), U52.8 (VCC), U53.8 (VCC), U54.8 (VCC), U55.8 (VCC), U56.8 (VCC), U57.8 (VCC), U58.8 (VCC), U59.8 (VCC), U60.8 (VCC), U61.8 (VCC), U62.8 (VCC), U63.8 (VCC), U65.8 (VCC), U66.6 (INM2), U66.8 (VCC), U67.8 (VCC), U68.8 (VCC), U69.8 (VCC), U70.8 (VCC), U71.8 (VCC), U72.8 (VCC); also elsewhere on the board
V12_DRIVER: R201.1 (A), R203.1 (A); also elsewhere on the board
WATCHDOG_OK: R176.1 (A), U42.7 (WDO_N), U44.6 (B2)
WD_CWD: R177.1 (A), U42.2 (CWD)
WD_HEARTBEAT: U42.6 (WDI); also elsewhere on the board

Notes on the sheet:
Independent IL INA293 + comparator -> async latch clear -> PWM AND + EN LOW, plus HRTIM FLT1.
Port INA293 pairs + TLV3202 windows + AND. No ADC polling in OC path; maximum delay unverified.
Hardware cell permission requires BQ provisioning; missing/invalid commissioning inhibits startup.
Thermal comparator hot/short/open window; source supply/shared sensor/common shunt failures remain in FMEA.
External contacts release slower than gate kill; coil current/release/fuse coordination require separate review.

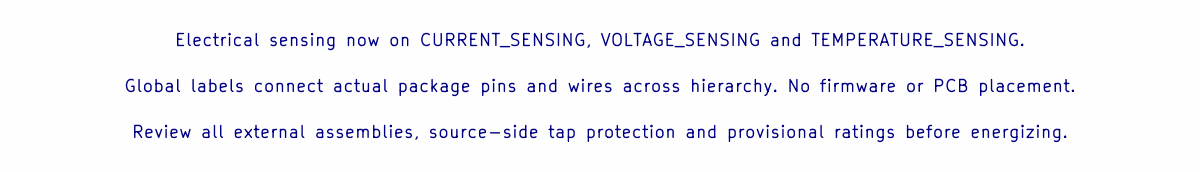
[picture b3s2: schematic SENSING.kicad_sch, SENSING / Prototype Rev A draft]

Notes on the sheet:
Electrical sensing now on CURRENT_SENSING, VOLTAGE_SENSING and TEMPERATURE_SENSING.
Global labels connect actual package pins and wires across hierarchy. No firmware or PCB placement.
Review all external assemblies, source-side tap protection and provisional ratings before energizing.

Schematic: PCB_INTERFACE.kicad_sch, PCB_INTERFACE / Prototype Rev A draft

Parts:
J19: ACTUATOR_12V / soldered harness with fixture stra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; SolderWire-0.5sqmm_1x01_D0.9mm_OD2.1mm
J20: BANK_P_RAW / soldered harness with fixture strain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; SolderWire-0.5sqmm_1x01_D0.9mm_OD2.1mm
J21: BUS_FUSED / soldered harness with fixture strain 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; SolderWire-2sqmm_1x01_D2mm_OD3.9mm
J22: BUS_ISO_COIL_M / soldered harness with fixture st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; SolderWire-0.5sqmm_1x01_D0.9mm_OD2.1mm
J23: BUS_ISO_FB / soldered harness with fixture strain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; SolderWire-0.5sqmm_1x01_D0.9mm_OD2.1mm
J24: BUS_LINK_IN / soldered harness with fixture strai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; SolderWire-2sqmm_1x01_D2mm_OD3.9mm
J25: BYP_BUS_COIL_M / soldered harness with fixture st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; SolderWire-0.5sqmm_1x01_D0.9mm_OD2.1mm
J26: BYP_BUS_FB / soldered harness with fixture strain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; SolderWire-0.5sqmm_1x01_D0.9mm_OD2.1mm
J27: BYP_CAP_COIL_M / soldered harness with fixture st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; SolderWire-0.5sqmm_1x01_D0.9mm_OD2.1mm
J28: BYP_CAP_FB / soldered harness with fixture strain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; SolderWire-0.5sqmm_1x01_D0.9mm_OD2.1mm
J29: CAN_H / soldered harness with fixture strain reli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; SolderWire-0.5sqmm_1x01_D0.9mm_OD2.1mm
J30: CAN_L / soldered harness with fixture strain reli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; SolderWire-0.5sqmm_1x01_D0.9mm_OD2.1mm
J31: CAP_ISO_COIL_M / soldered harness with fixture st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; SolderWire-0.5sqmm_1x01_D0.9mm_OD2.1mm
J32: CAP_ISO_FB / soldered harness with fixture strain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; SolderWire-0.5sqmm_1x01_D0.9mm_OD2.1mm
J33: CAP_LINK_IN / soldered harness with fixture strai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; SolderWire-2sqmm_1x01_D2mm_OD3.9mm
J34: DUMP_DRAIN / soldered harness with fixture strain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; SolderWire-0.5sqmm_1x01_D0.9mm_OD2.1mm
J35: GND / soldered harness with fixture strain relief; SolderWire-2sqmm_1x01_D2mm_OD3.9mm
J36: PRE_BUS_LED_M / soldered harness with fixture str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; SolderWire-0.5sqmm_1x01_D0.9mm_OD2.1mm
J37: PRE_BUS_LED_P / soldered harness with fixture str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; SolderWire-0.5sqmm_1x01_D0.9mm_OD2.1mm
J38: PRE_CAP_LED_M / soldered harness with fixture str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; SolderWire-0.5sqmm_1x01_D0.9mm_OD2.1mm
J39: PRE_CAP_LED_P / soldered harness with fixture str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; SolderWire-0.5sqmm_1x01_D0.9mm_OD2.1mm
J40: REFEREE_PERMIT / soldered harness with fixture st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; SolderWire-0.5sqmm_1x01_D0.9mm_OD2.1mm
J41: TAP0_SOURCE_PROTECTED / soldered harness with fix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; SolderWire-0.5sqmm_1x01_D0.9mm_OD2.1mm
J42: TAP1_SOURCE_PROTECTED / soldered harness with fix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; SolderWire-0.5sqmm_1x01_D0.9mm_OD2.1mm
J43: TAP2_SOURCE_PROTECTED / soldered harness with fix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; SolderWire-0.5sqmm_1x01_D0.9mm_OD2.1mm
J44: TAP3_SOURCE_PROTECTED / soldered harness with fix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; SolderWire-0.5sqmm_1x01_D0.9mm_OD2.1mm
J45: TAP4_SOURCE_PROTECTED / soldered harness with fix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; SolderWire-0.5sqmm_1x01_D0.9mm_OD2.1mm
J46: TAP5_SOURCE_PROTECTED / soldered harness with fix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; SolderWire-0.5sqmm_1x01_D0.9mm_OD2.1mm
J47: TAP6_SOURCE_PROTECTED / soldered harness with fix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; SolderWire-0.5sqmm_1x01_D0.9mm_OD2.1mm
J48: TAP7_SOURCE_PROTECTED / soldered harness with fix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; SolderWire-0.5sqmm_1x01_D0.9mm_OD2.1mm
J49: TAP8_SOURCE_PROTECTED / soldered harness with fix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; SolderWire-0.5sqmm_1x01_D0.9mm_OD2.1mm
J50: TAP9_SOURCE_PROTECTED / soldered harness with fix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; SolderWire-0.5sqmm_1x01_D0.9mm_OD2.1mm

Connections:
ACTUATOR_12V: J19.1; also elsewhere on the board
BANK_P_RAW: J20.1; also elsewhere on the board
BUS_FUSED: J21.1; also elsewhere on the board
BUS_ISO_COIL_M: J22.1; also elsewhere on the board
BUS_ISO_FB: J23.1; also elsewhere on the board
BUS_LINK_IN: J24.1; also elsewhere on the board
BYP_BUS_COIL_M: J25.1; also elsewhere on the board
BYP_BUS_FB: J26.1; also elsewhere on the board
BYP_CAP_COIL_M: J27.1; also elsewhere on the board
BYP_CAP_FB: J28.1; also elsewhere on the board
CAN_H: J29.1; also elsewhere on the board
CAN_L: J30.1; also elsewhere on the board
CAP_ISO_COIL_M: J31.1; also elsewhere on the board
CAP_ISO_FB: J32.1; also elsewhere on the board
CAP_LINK_IN: J33.1; also elsewhere on the board
DUMP_DRAIN: J34.1; also elsewhere on the board
GND: J35.1; also elsewhere on the board
PRE_BUS_LED_M: J36.1; also elsewhere on the board
PRE_BUS_LED_P: J37.1; also elsewhere on the board
PRE_CAP_LED_M: J38.1; also elsewhere on the board
PRE_CAP_LED_P: J39.1; also elsewhere on the board
REFEREE_PERMIT: J40.1; also elsewhere on the board
TAP0_SOURCE_PROTECTED: J41.1; also elsewhere on the board
TAP1_SOURCE_PROTECTED: J42.1; also elsewhere on the board
TAP2_SOURCE_PROTECTED: J43.1; also elsewhere on the board
TAP3_SOURCE_PROTECTED: J44.1; also elsewhere on the board
TAP4_SOURCE_PROTECTED: J45.1; also elsewhere on the board
TAP5_SOURCE_PROTECTED: J46.1; also elsewhere on the board
TAP6_SOURCE_PROTECTED: J47.1; also elsewhere on the board
TAP7_SOURCE_PROTECTED: J48.1; also elsewhere on the board
TAP8_SOURCE_PROTECTED: J49.1; also elsewhere on the board
TAP9_SOURCE_PROTECTED: J50.1; also elsewhere on the board

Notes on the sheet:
Bench prototype only: wire lands are NOT plug connectors. Harness continuity/polarity inspection mandatory.
External isolation/fuses/precharge/cells remain separate. Each named terminal is a distinct net; do not bridge protection.
2026-10-04 user authorized PCB work without preceding hardware measurement. No fabrication or energizing release.
